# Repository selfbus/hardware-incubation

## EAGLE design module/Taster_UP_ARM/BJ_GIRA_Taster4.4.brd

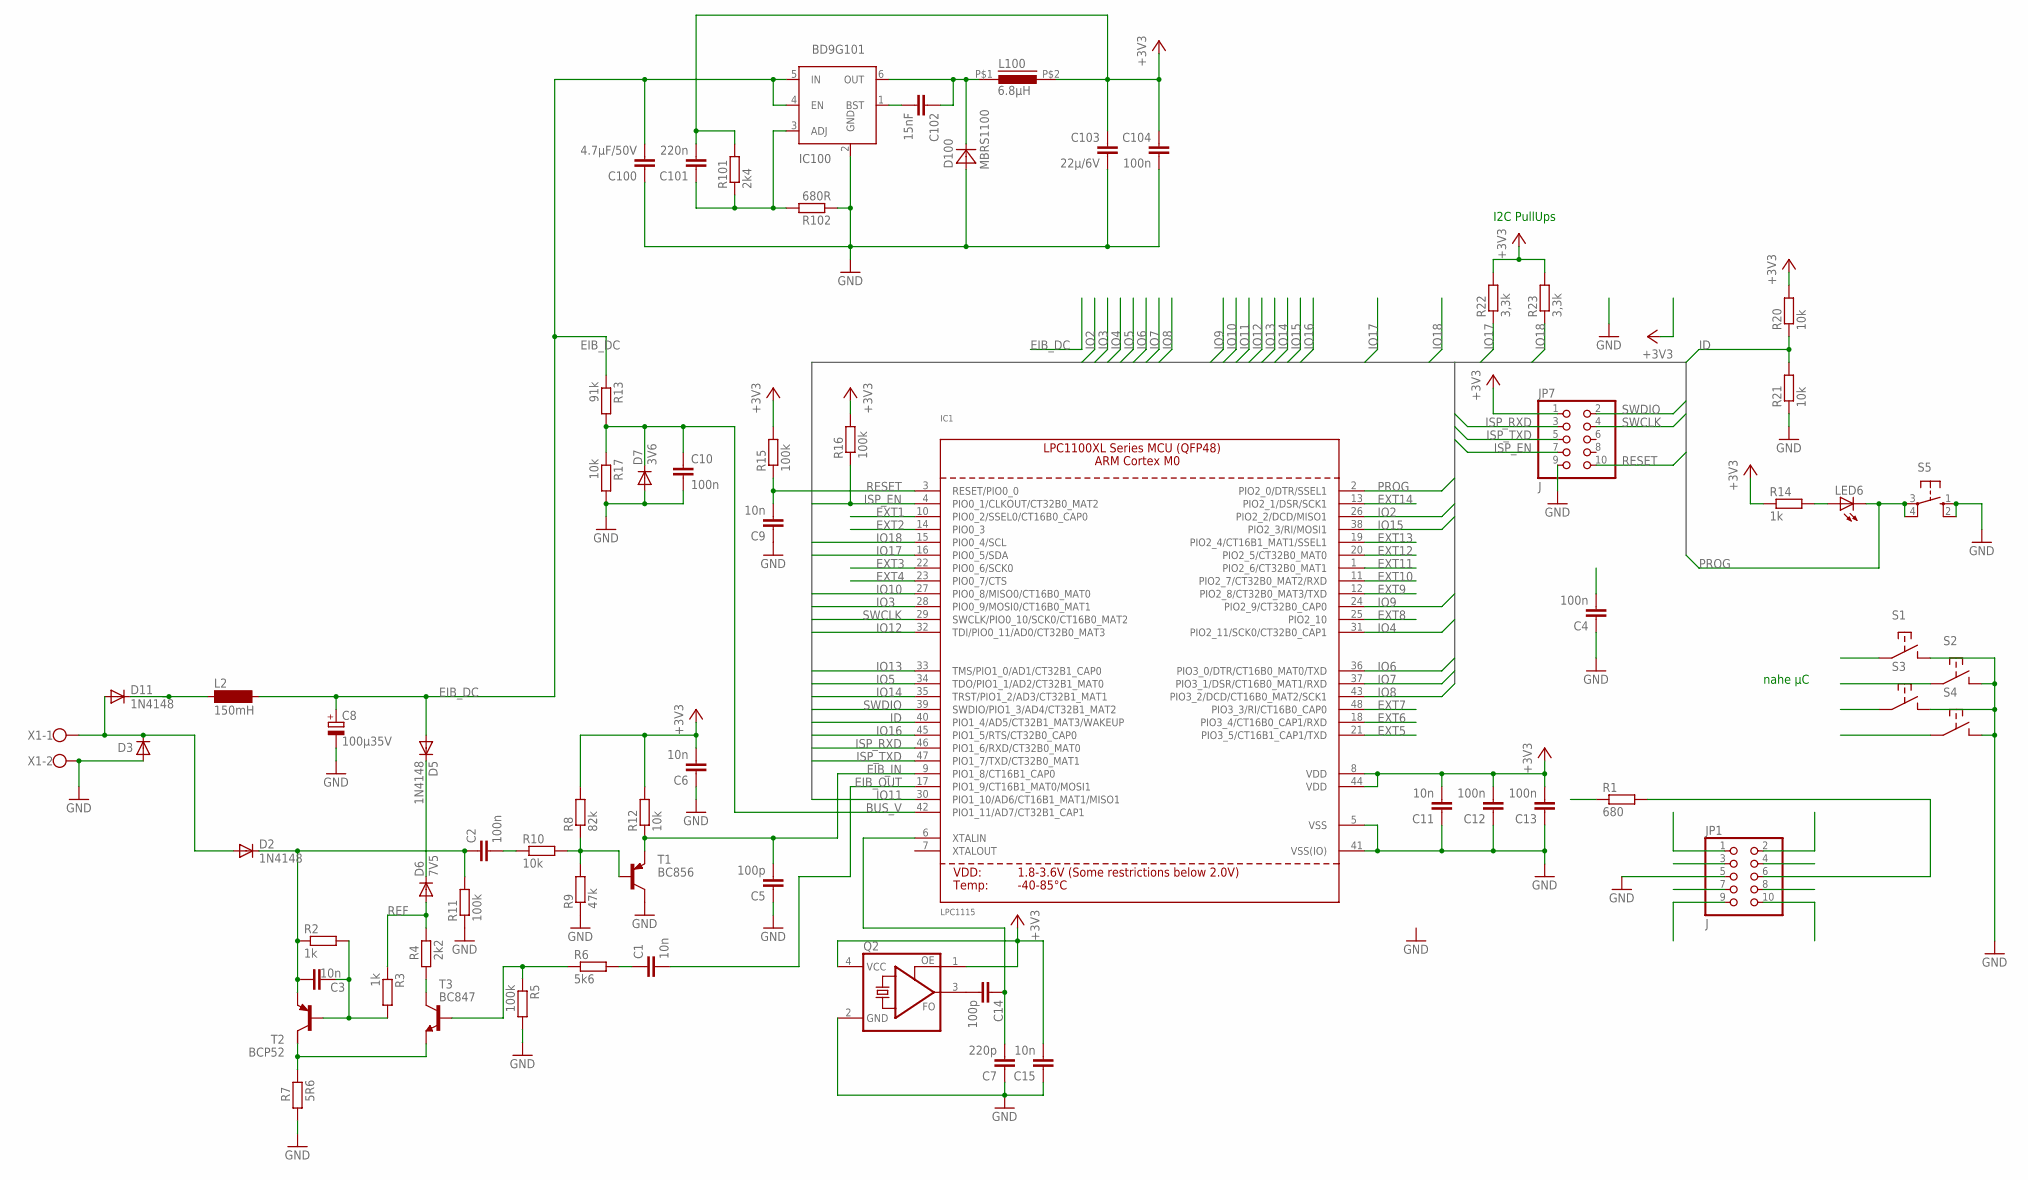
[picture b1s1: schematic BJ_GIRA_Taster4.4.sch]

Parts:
C1, C3, C6, C9, C11, C15: 10n; C1206
C2, C4, C10, C12, C13, C104: 100n; C1206
C5, C14: 100p; C1206
C7: 220p; C1206
C8: 100µ35V; E3,5-8
C100: 4.7µF/50V; C1206
C101: 220n; C1206
C102: 15nF; C1206
C103: 22µ/6V; C1206
D2, D5, D11: 1N4148; MINIMELF
D3: D-SMB; SMB
D6: 7V5; MINIMELF
D7: 3V6; MINIMELF
D100: MBRS1100; SMA
IC1: LPC1115; LQFP48
IC100: BD9G101; SOT23-6
JP1, JP7: J; 2X05M
L2: 150mH; BS11
L100: 6.8µH; PIS2812
LED6: LED3MM
Q2: ASFL; ASF
R1: 680; R1206
R2, R3, R14: 1k; R1206
R4: 2k2; R1206
R5, R11, R15, R16: 100k; R1206
R6: 5k6; R1206
R7: 5R6; R1206
R8: 82k; R1206
R9: 47k; R1206
R10, R12, R17, R20, R21: 10k; R1206
R13: 91k; R1206
R22, R23: 3,3k; R1206
R101: 2k4; R1206
R102: 680R; R1206
S1, S2, S3, S4: 33053305A; 3305A
S5: 10-XX; B3F-10XX
T1: BC856; SOT23-BEC
T2: BCP52; SOT223
T3: BC847; SOT23
X1: W237-02P; W237-132

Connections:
+3V3: C6.2, C11.2, C12.2, C13.2, C15.2, C101.2, C103.1, C104.1, IC1.8 (VDD), IC1.44 (VDD), JP1.4, JP7.1, L100.P$2 (2), Q2.1 (OE), Q2.4 (VCC), R8.2, R12.2, R14.1, R15.2, R16.2, R20.2, R22.2, R23.2, R101.2
BUS_V: C10.2, D7.C, IC1.42 (PIO1_11/AD7/CT32B1_CAP1), R13.2, R17.1
DRAIN: C2.1, C3.1, D2.C, R2.1, R11.2, T2.3 (E)
EIB+: D2.A, D3.1 (C), D11.A, X1.1
EIB_DC: C8.+, C100.2, D5.A, IC100.4 (EN), IC100.5 (IN), L2.2, R13.1
EIB_IN: C5.2, IC1.9 (PIO1_8/CT16B1_CAP0), R12.1, T1.E
EIB_OUT: C1.2, IC1.17 (PIO1_9/CT16B1_MAT0/MOSI1)
EXT1: IC1.10 (PIO0_2/SSEL0/CT16B0_CAP0)
EXT2: IC1.14 (PIO0_3)
EXT3: IC1.22 (PIO0_6/SCK0)
EXT4: IC1.23 (PIO0_7/CTS), S2.P$1 (1)
EXT5: IC1.21 (PIO3_5/CT16B1_CAP1/TXD), JP1.7
EXT6: IC1.18 (PIO3_4/CT16B0_CAP1/RXD), JP1.8
EXT7: IC1.48 (PIO3_3/RI/CT16B0_CAP0), S1.P$1 (1)
EXT8: IC1.25 (PIO2_10), S3.P$1 (1)
EXT9: IC1.12 (PIO2_8/CT32B0_MAT3/TXD)
EXT10: IC1.11 (PIO2_7/CT32B0_MAT2/RXD)
EXT11: IC1.1 (PIO2_6/CT32B0_MAT1), JP1.10, R1.1
EXT12: IC1.20 (PIO2_5/CT32B0_MAT0)
EXT13: IC1.19 (PIO2_4/CT16B1_MAT1/SSEL1)
EXT14: IC1.13 (PIO2_1/DSR/SCK1), JP1.1
GND: C4.1, C5.1, C6.1, C7.1, C8.-, C9.1, C10.1, C11.1, C12.1, C13.1, C15.1, C100.1, C103.2, C104.2, D3.2 (A), D7.A, D100.A, IC1.5 (VSS), IC1.41 (VSS(IO)), IC100.2 (GND), JP1.5, JP7.9, Q2.2 (GND), R5.2, R7.1, R9.1, R11.1, R17.2, R21.1, R102.1, S1.P$2 (2), S2.P$2 (2), S3.P$2 (2), S4.P$2 (2), S5.1 (S), S5.2 (S1), T1.C, X1.2
ID: IC1.40 (PIO1_4/AD5/CT32B1_MAT3/WAKEUP), R20.1, R21.2
IO2: IC1.26 (PIO2_2/DCD/MISO1), JP1.2
IO3: IC1.28 (PIO0_9/MOSI0/CT16B0_MAT1)
IO4: IC1.31 (PIO2_11/SCK0/CT32B0_CAP1), JP1.3
IO5: IC1.34 (TDO/PIO1_1/AD2/CT32B1_MAT0)
IO6: IC1.36 (PIO3_0/DTR/CT16B0_MAT0/TXD)
IO7: IC1.37 (PIO3_1/DSR/CT16B0_MAT1/RXD)
IO8: IC1.43 (PIO3_2/DCD/CT16B0_MAT2/SCK1)
IO9: IC1.24 (PIO2_9/CT32B0_CAP0), S4.P$1 (1)
IO10: IC1.27 (PIO0_8/MISO0/CT16B0_MAT0)
IO11: IC1.30 (PIO1_10/AD6/CT16B1_MAT1/MISO1)
IO12: IC1.32 (TDI/PIO0_11/AD0/CT32B0_MAT3)
IO13: IC1.33 (TMS/PIO1_0/AD1/CT32B1_CAP0)
IO14: IC1.35 (TRST/PIO1_2/AD3/CT32B1_MAT1)
IO15: IC1.38 (PIO2_3/RI/MOSI1), JP1.9
IO16: IC1.45 (PIO1_5/RTS/CT32B0_CAP0)
IO17: IC1.16 (PIO0_5/SDA), R22.1
IO18: IC1.15 (PIO0_4/SCL), R23.1
ISP_EN: IC1.4 (PIO0_1/CLKOUT/CT32B0_MAT2), JP7.7, R16.1
ISP_RXD: IC1.46 (PIO1_6/RXD/CT32B0_MAT0), JP7.3
ISP_TXD: IC1.47 (PIO1_7/TXD/CT32B0_MAT1), JP7.5
LX: C102.1, D100.C, IC100.6 (OUT), L100.P$1 (1)
unnamed: C2.2, R10.1
unnamed: C101.1, IC100.3 (ADJ), R101.1, R102.2
unnamed: R4.1, T3.3 (C)
unnamed: JP1.6, R1.2
unnamed: LED6.A, R14.2
unnamed: C1.1, R6.2
unnamed: C3.2, R2.2, R3.2, T2.1 (B)
unnamed: R5.1, R6.1, T3.1 (B)
unnamed: R7.2, T2.2 (C), T3.2 (E)
unnamed: R8.1, R9.2, R10.2, T1.B
unnamed: D5.C, D6.C
unnamed: C7.2, C14.1, IC1.6 (XTALIN)
unnamed: C14.2, Q2.3 (FO)
unnamed: C102.2, IC100.1 (BST)
unnamed: D11.C, L2.1
PROG: IC1.2 (PIO2_0/DTR/SSEL1), LED6.K (C), S5.3, S5.4 (P1)
REF: D6.A, R3.1, R4.2
RESET: C9.2, IC1.3 (RESET/PIO0_0), JP7.10, R15.1
SWCLK: IC1.29 (SWCLK/PIO0_10/SCK0/CT16B0_MAT2), JP7.4
SWDIO: IC1.39 (SWDIO/PIO1_3/AD4/CT32B1_MAT2), JP7.2
VCC_LPC: C4.2

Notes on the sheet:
nahe µC
I2C PullUps

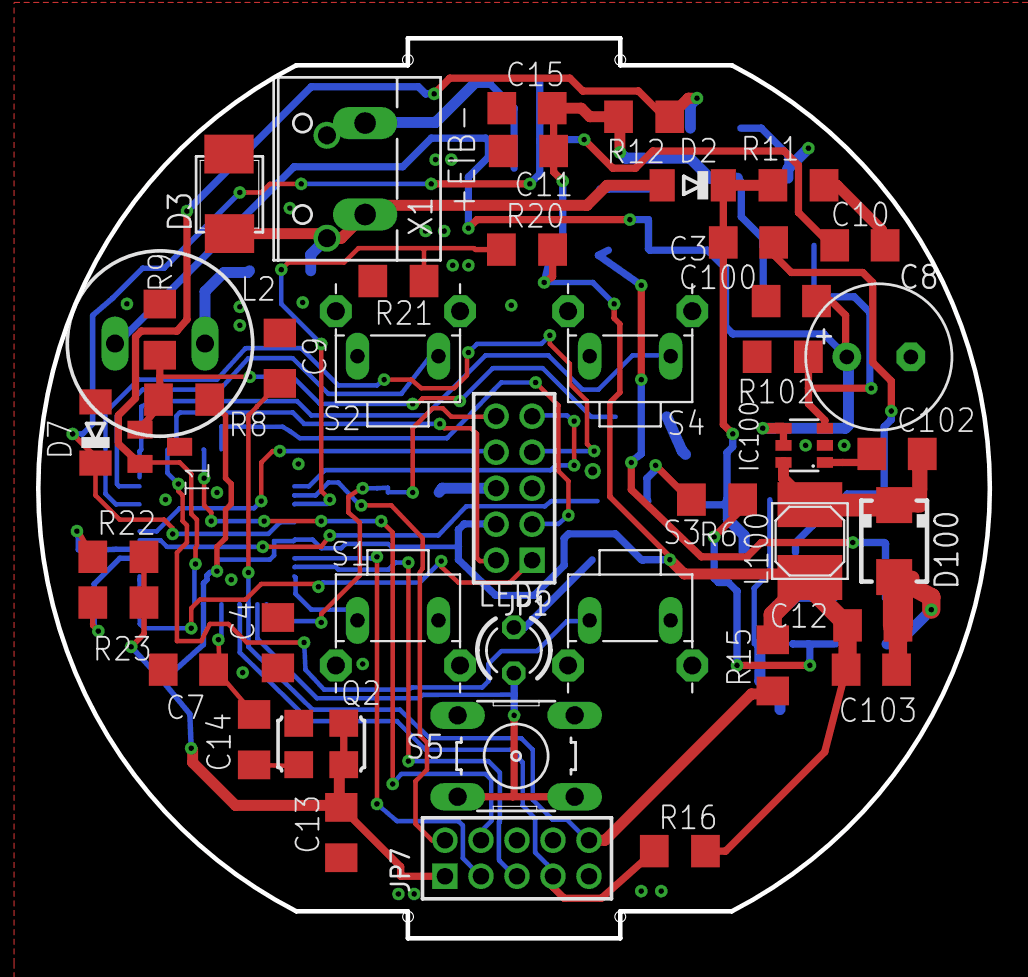
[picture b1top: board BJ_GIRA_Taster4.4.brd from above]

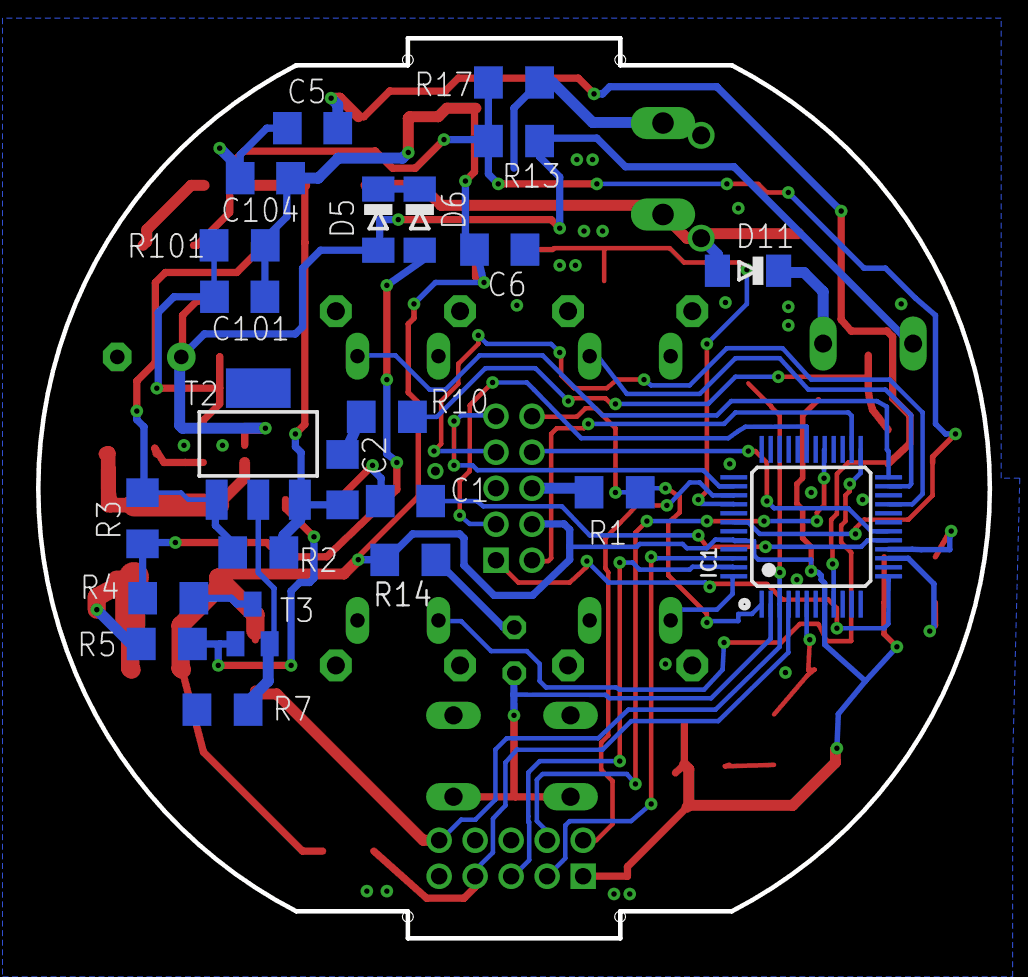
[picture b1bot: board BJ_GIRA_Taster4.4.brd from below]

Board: 2 copper layers, 52.9 x 50.0 mm, 67 parts (23 on the bottom side), 46 nets.

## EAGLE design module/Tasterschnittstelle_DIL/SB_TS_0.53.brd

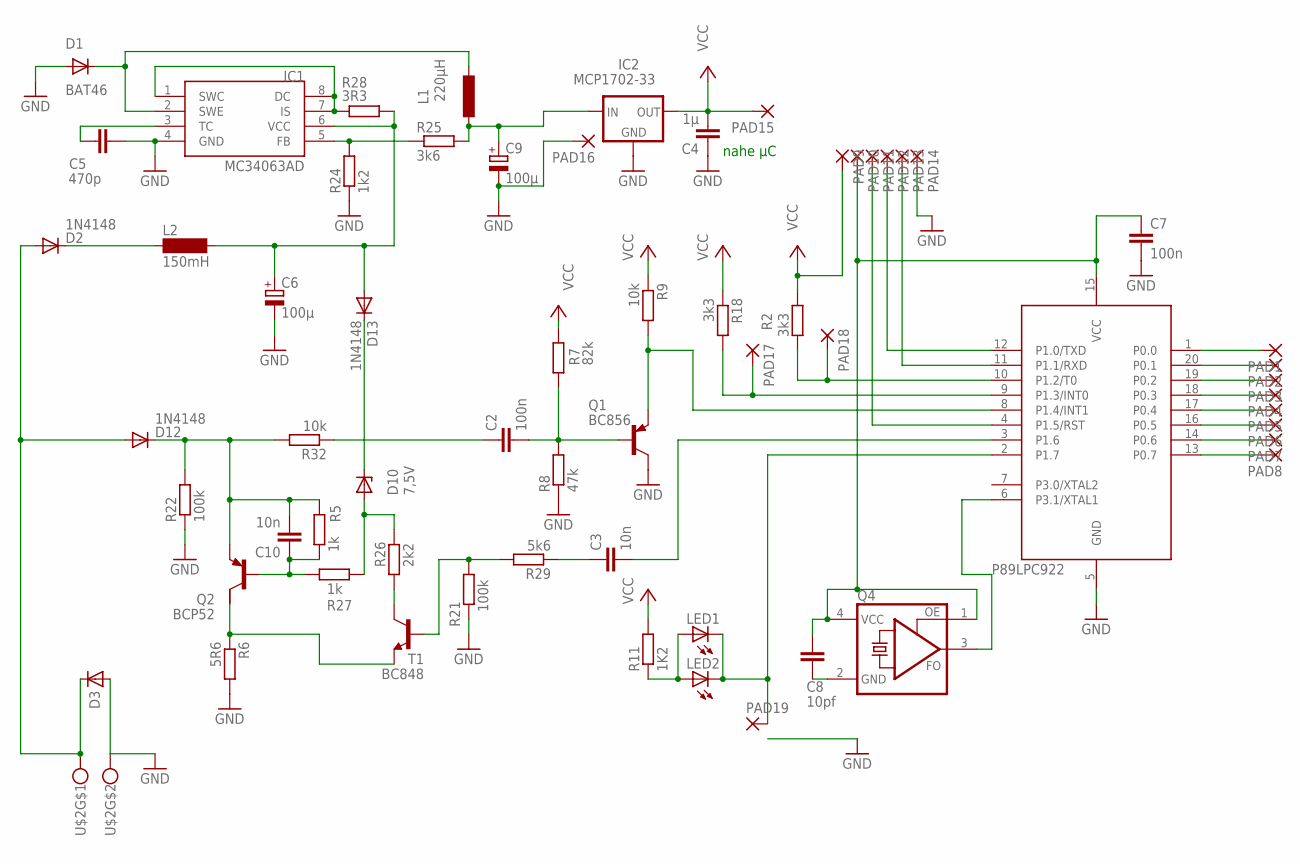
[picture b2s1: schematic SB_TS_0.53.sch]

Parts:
C2, C7: 100n; C1206
C3, C10: 10n; C1206
C4: 1µ; C1206
C5: 470p; C1206
C6: 100µ; E5-8,5
C8: 10pf; C1206
C9: 100µ; E2,5-5
D1: BAT46; MINIMELF
D2, D12, D13: 1N4148; MINIMELF
D3: SMAJ40AC; SMB
D10: 7,5V; MINIMELF
IC1: MC34063AD; SOIC8
IC2: MCP1702-33; 79LXX
L1: 220µH; 2200-11.43
L2: 150mH; SD12_1000
LED1: LEDCHIPLED_1206; CHIPLED_1206
LED2: LED3MM
PAD1, PAD2, PAD3, PAD4, PAD5, PAD6, PAD7, PAD8, PAD9, PAD10, PAD11, PAD12, PAD13, PAD14, PAD15, PAD16, PAD17, PAD18, PAD19: SMD2; SMD1,27-2,54
Q1: BC856; SOT23-BEC
Q2: BCP52; SOT223
Q4: ASFL; ASF
R2: 3k3; M1206
R5, R27: 1k; R1206
R6: 5R6; R1206
R7: 82k; R1206
R8: 47k; M1206
R9, R32: 10k; R1206
R11: 1K2; R1206
R18: 3k3; R1206
R21: 100k; R1206
R22: 100k; M1206
R24: 1k2; R1206
R25: 3k6; M1206
R26: 2k2; M1206
R28: 3R3; M1206
R29: 5k6; R1206
T1: BC848; SOT23
U1: 89LPC922; DIL20
U$2: AKL059-02; AKL3.5X2

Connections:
A_PUNKT_EIBIN: C2.2, Q1.B, R7.1, R8.2
BASE_SEND: R21.2, R29.2, T1.1 (B)
BASE_SEND_AMP: C10.1, Q2.1 (B), R5.1, R27.2
CURR_SENSE: Q2.2 (C), R6.1, T1.2 (E)
C_T1: R26.1, T1.3 (C)
EIB+: D2.A, D3.1 (C), D12.A, U$2.1
EIBIN: Q1.E, R9.2, U1.8 (P1.4/INT1)
EIB_DC1: C6.+, D13.A, IC1.6 (VCC), L2.2, R28.2
EIB_SEND: C3.2, U1.3 (P1.6)
GND: C4.1, C5.2, C6.-, C7.2, C9.-, D1.A, D3.2 (A), IC1.4 (GND), IC2.GND, PAD14.1, PAD16.1, Q1.C, R6.2, R8.1, R21.1, R22.1, R24.1, U1.5 (GND), U$2.2
INT0: PAD17.1, R18.2, U1.9 (P1.3/INT0)
unnamed: C3.1, R29.1
unnamed: C10.2, D12.C, Q2.3 (E), R5.2, R22.2, R32.2
unnamed: D2.C, L2.1
unnamed: LED1.A, LED2.A, R11.1
unnamed: C8.2, Q4.2 (GND)
unnamed: D1.C, IC1.2 (SWE), L1.2
unnamed: C5.1, IC1.3 (TC)
unnamed: D10.C, D13.C
unnamed: IC1.1 (SWC), IC1.7 (IS), IC1.8 (DC), R28.1
unnamed: C2.1, R32.1
OSCCLK: Q4.3 (FO), U1.6 (P3.1/XTAL1)
P00: PAD1.1, U1.1 (P0.0)
P01: PAD2.1, U1.20 (P0.1)
P02: PAD3.1, U1.19 (P0.2)
P03: PAD4.1, U1.18 (P0.3)
P04: PAD5.1, U1.17 (P0.4)
P05: PAD6.1, U1.16 (P0.5)
P06: PAD7.1, U1.14 (P0.6)
P07: PAD8.1, U1.13 (P0.7)
PROG: LED1.C, LED2.K (C), PAD19.1, U1.2 (P1.7)
PWM: PAD18.1, R2.2, U1.10 (P1.2/T0)
REFERENZ: D10.A, R26.2, R27.1
RESET: PAD11.1, U1.4 (P1.5/RST)
RXD: PAD13.1, U1.11 (P1.1/RXD)
TXD: PAD12.1, U1.12 (P1.0/TXD)
VCC: C4.2, IC2.OUT, PAD9.1, PAD15.1, R2.1, R7.2, R9.1, R11.2, R18.1
VCC5V: C9.+, IC2.IN, L1.1, R25.2
VCC_FEEDBACK: IC1.5 (FB), R24.2, R25.1
VCC_LPC: C7.1, C8.1, PAD10.1, Q4.1 (OE), Q4.4 (VCC), U1.15 (VCC)

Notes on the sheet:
nahe µC
P89LPC922

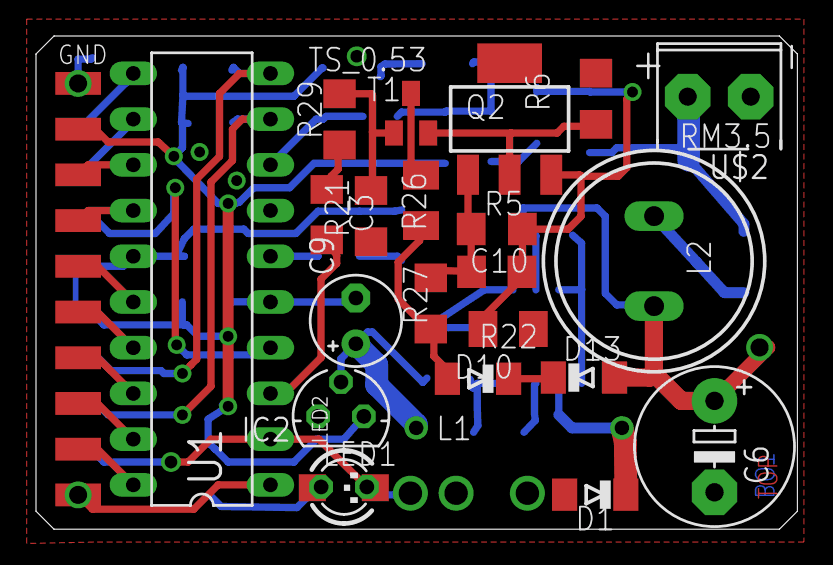
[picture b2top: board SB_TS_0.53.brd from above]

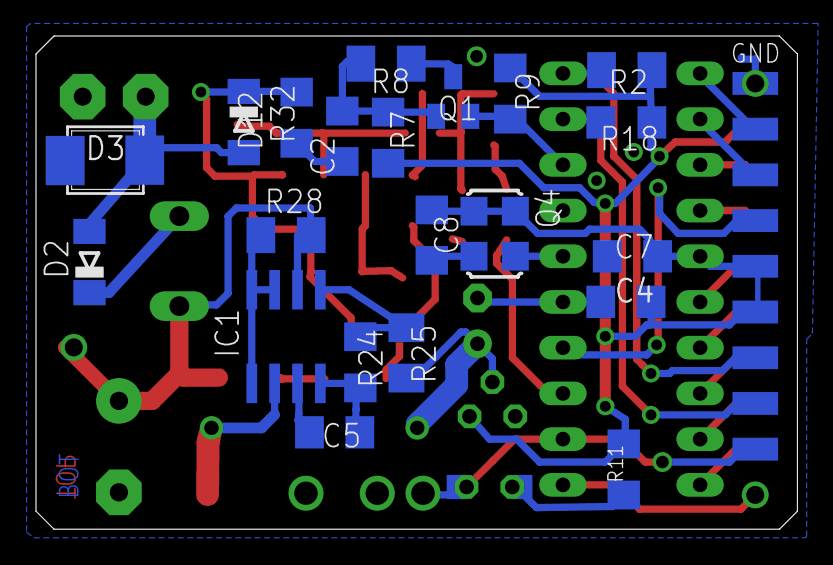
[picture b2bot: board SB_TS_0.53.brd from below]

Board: 2 copper layers, 42.3 x 27.4 mm, 63 parts (30 on the bottom side), 40 nets.

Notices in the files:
parts and their libraries:
microbuilder: This work is placed in the public domain, and may be freely used for commercial and non-commercial work with the following conditions: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
